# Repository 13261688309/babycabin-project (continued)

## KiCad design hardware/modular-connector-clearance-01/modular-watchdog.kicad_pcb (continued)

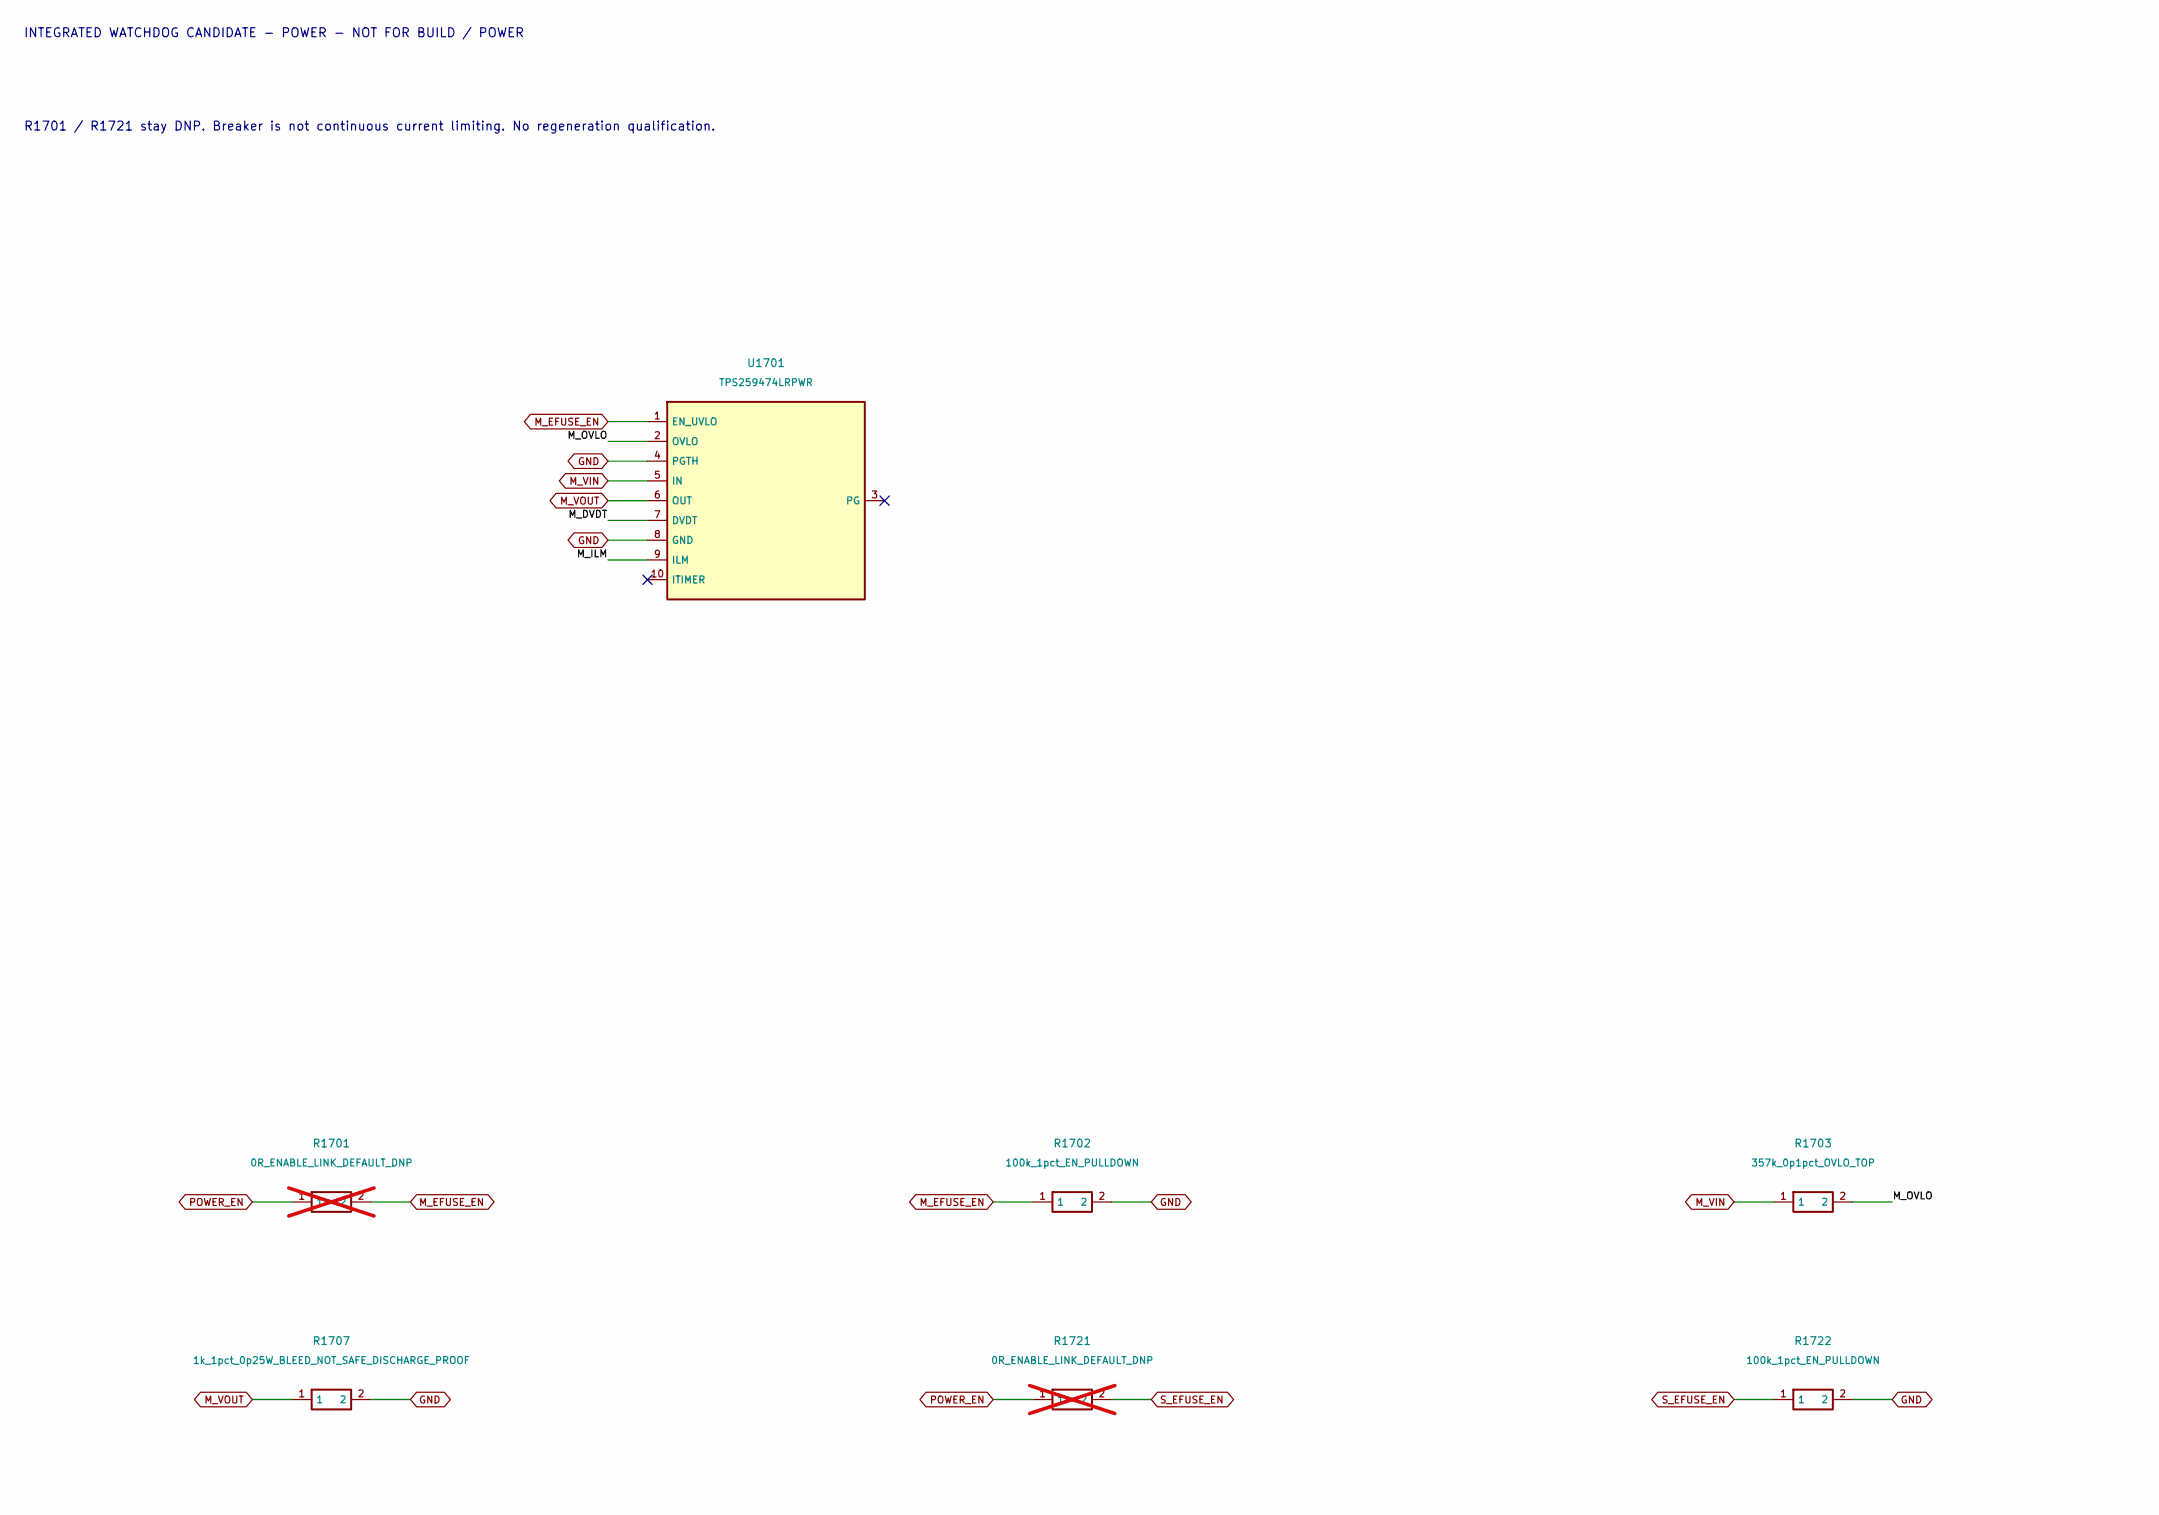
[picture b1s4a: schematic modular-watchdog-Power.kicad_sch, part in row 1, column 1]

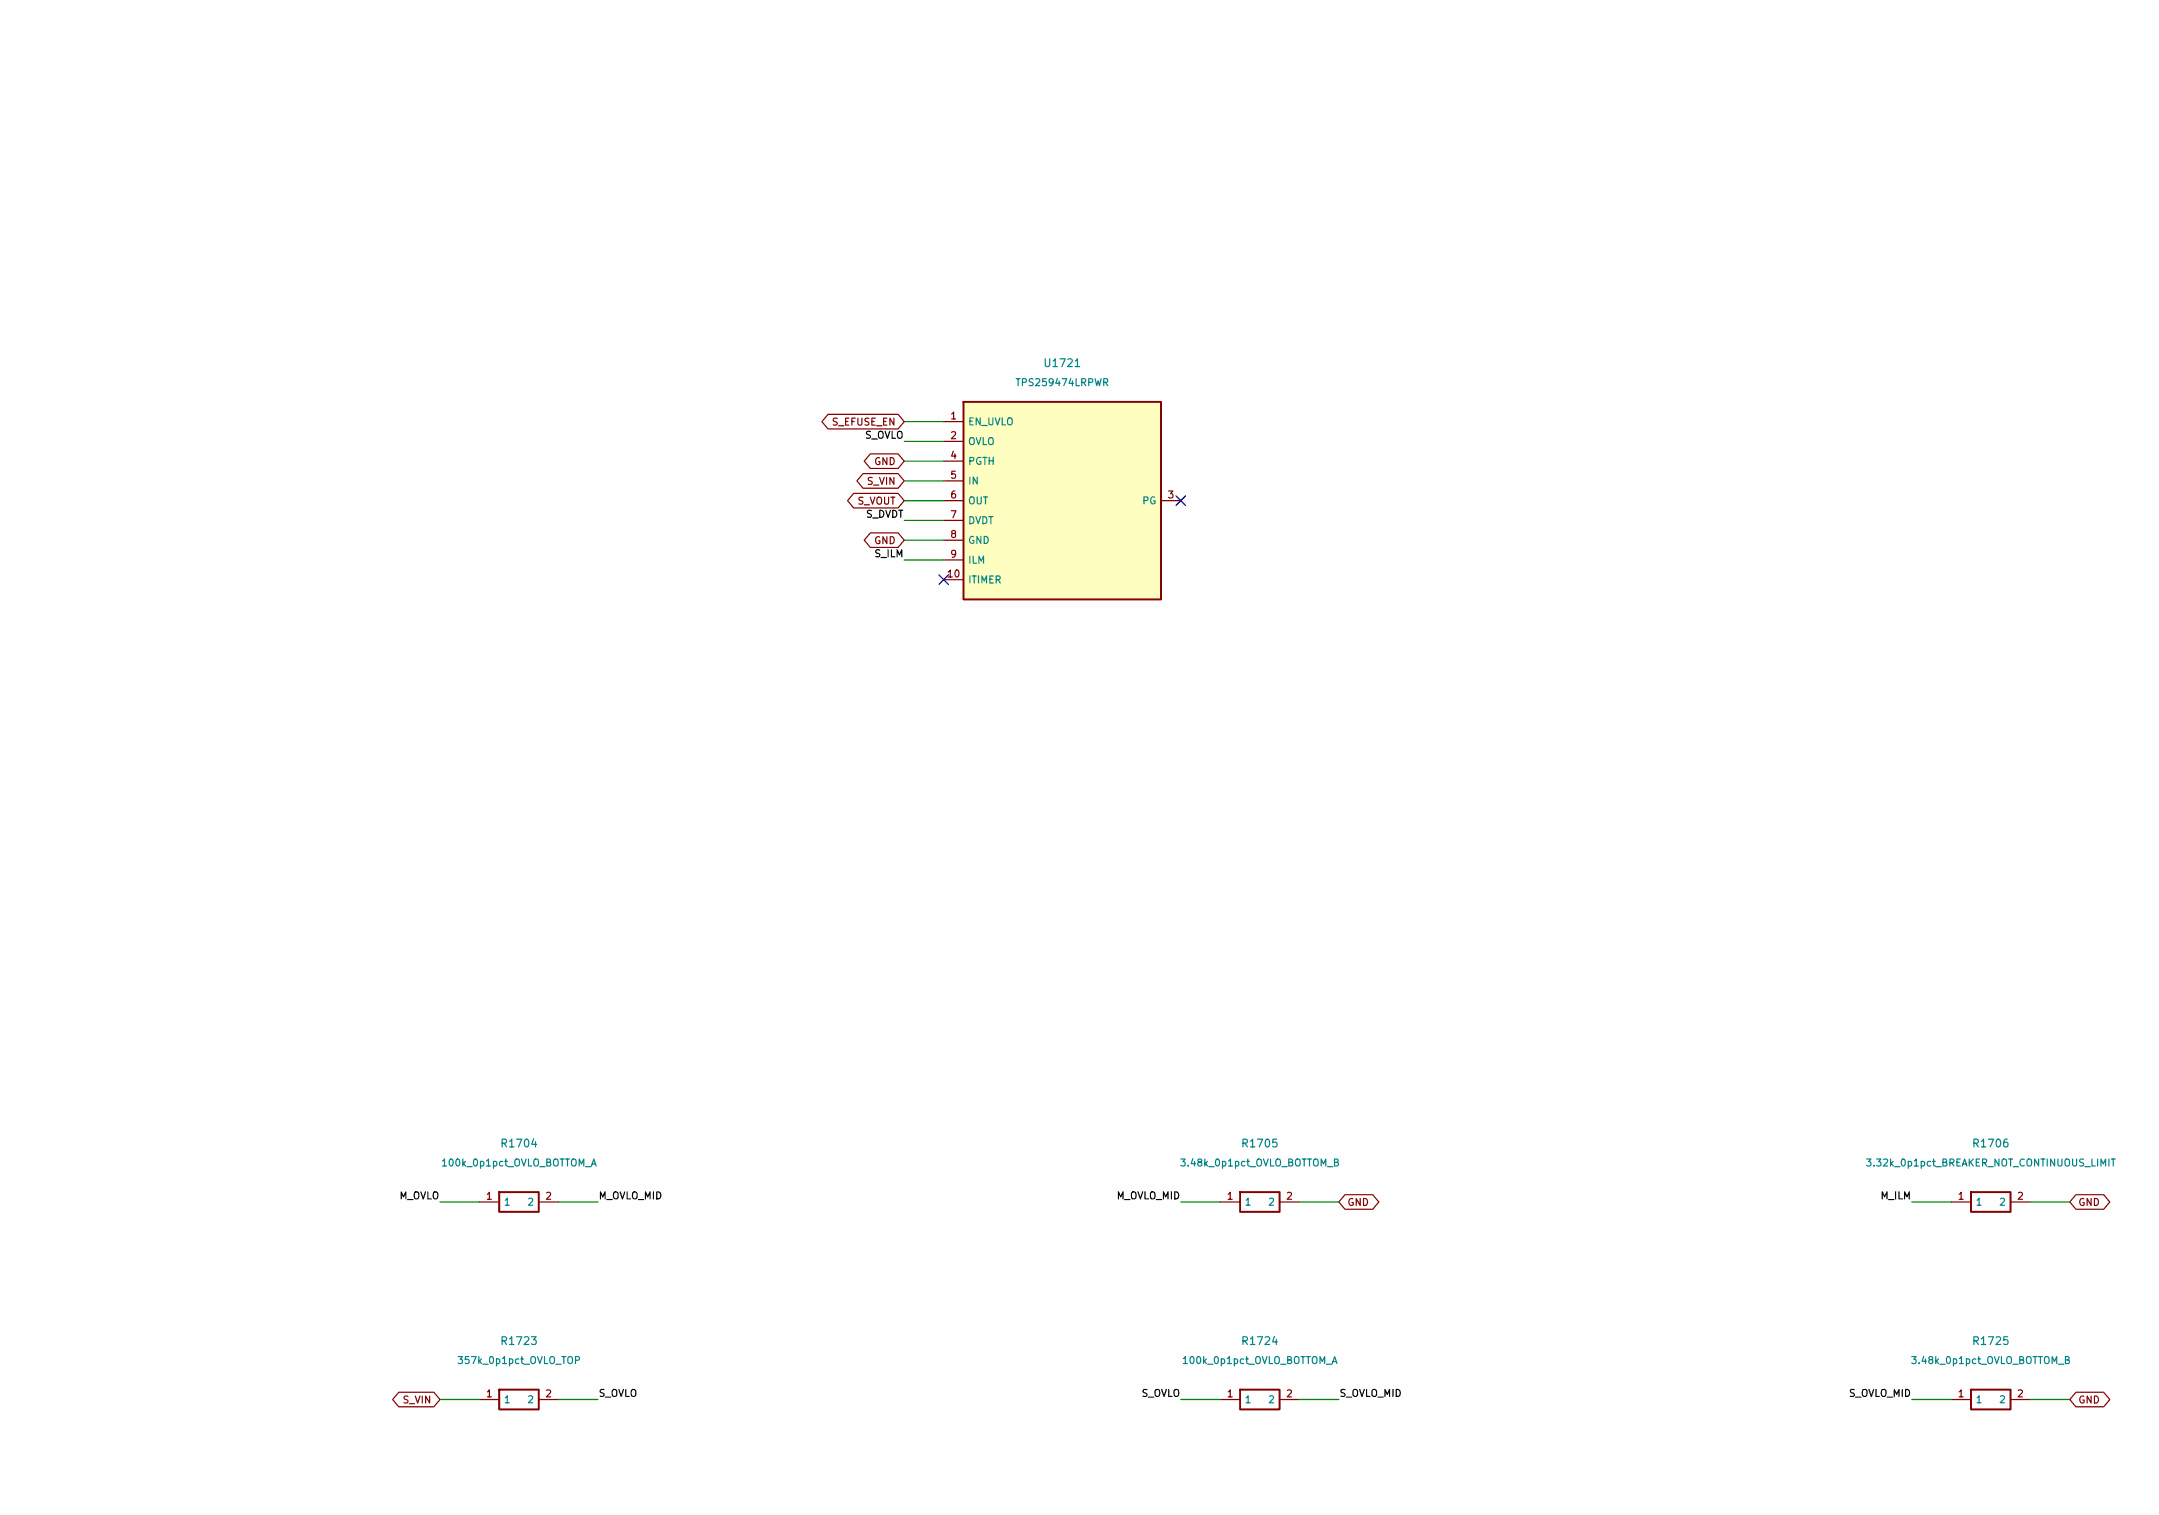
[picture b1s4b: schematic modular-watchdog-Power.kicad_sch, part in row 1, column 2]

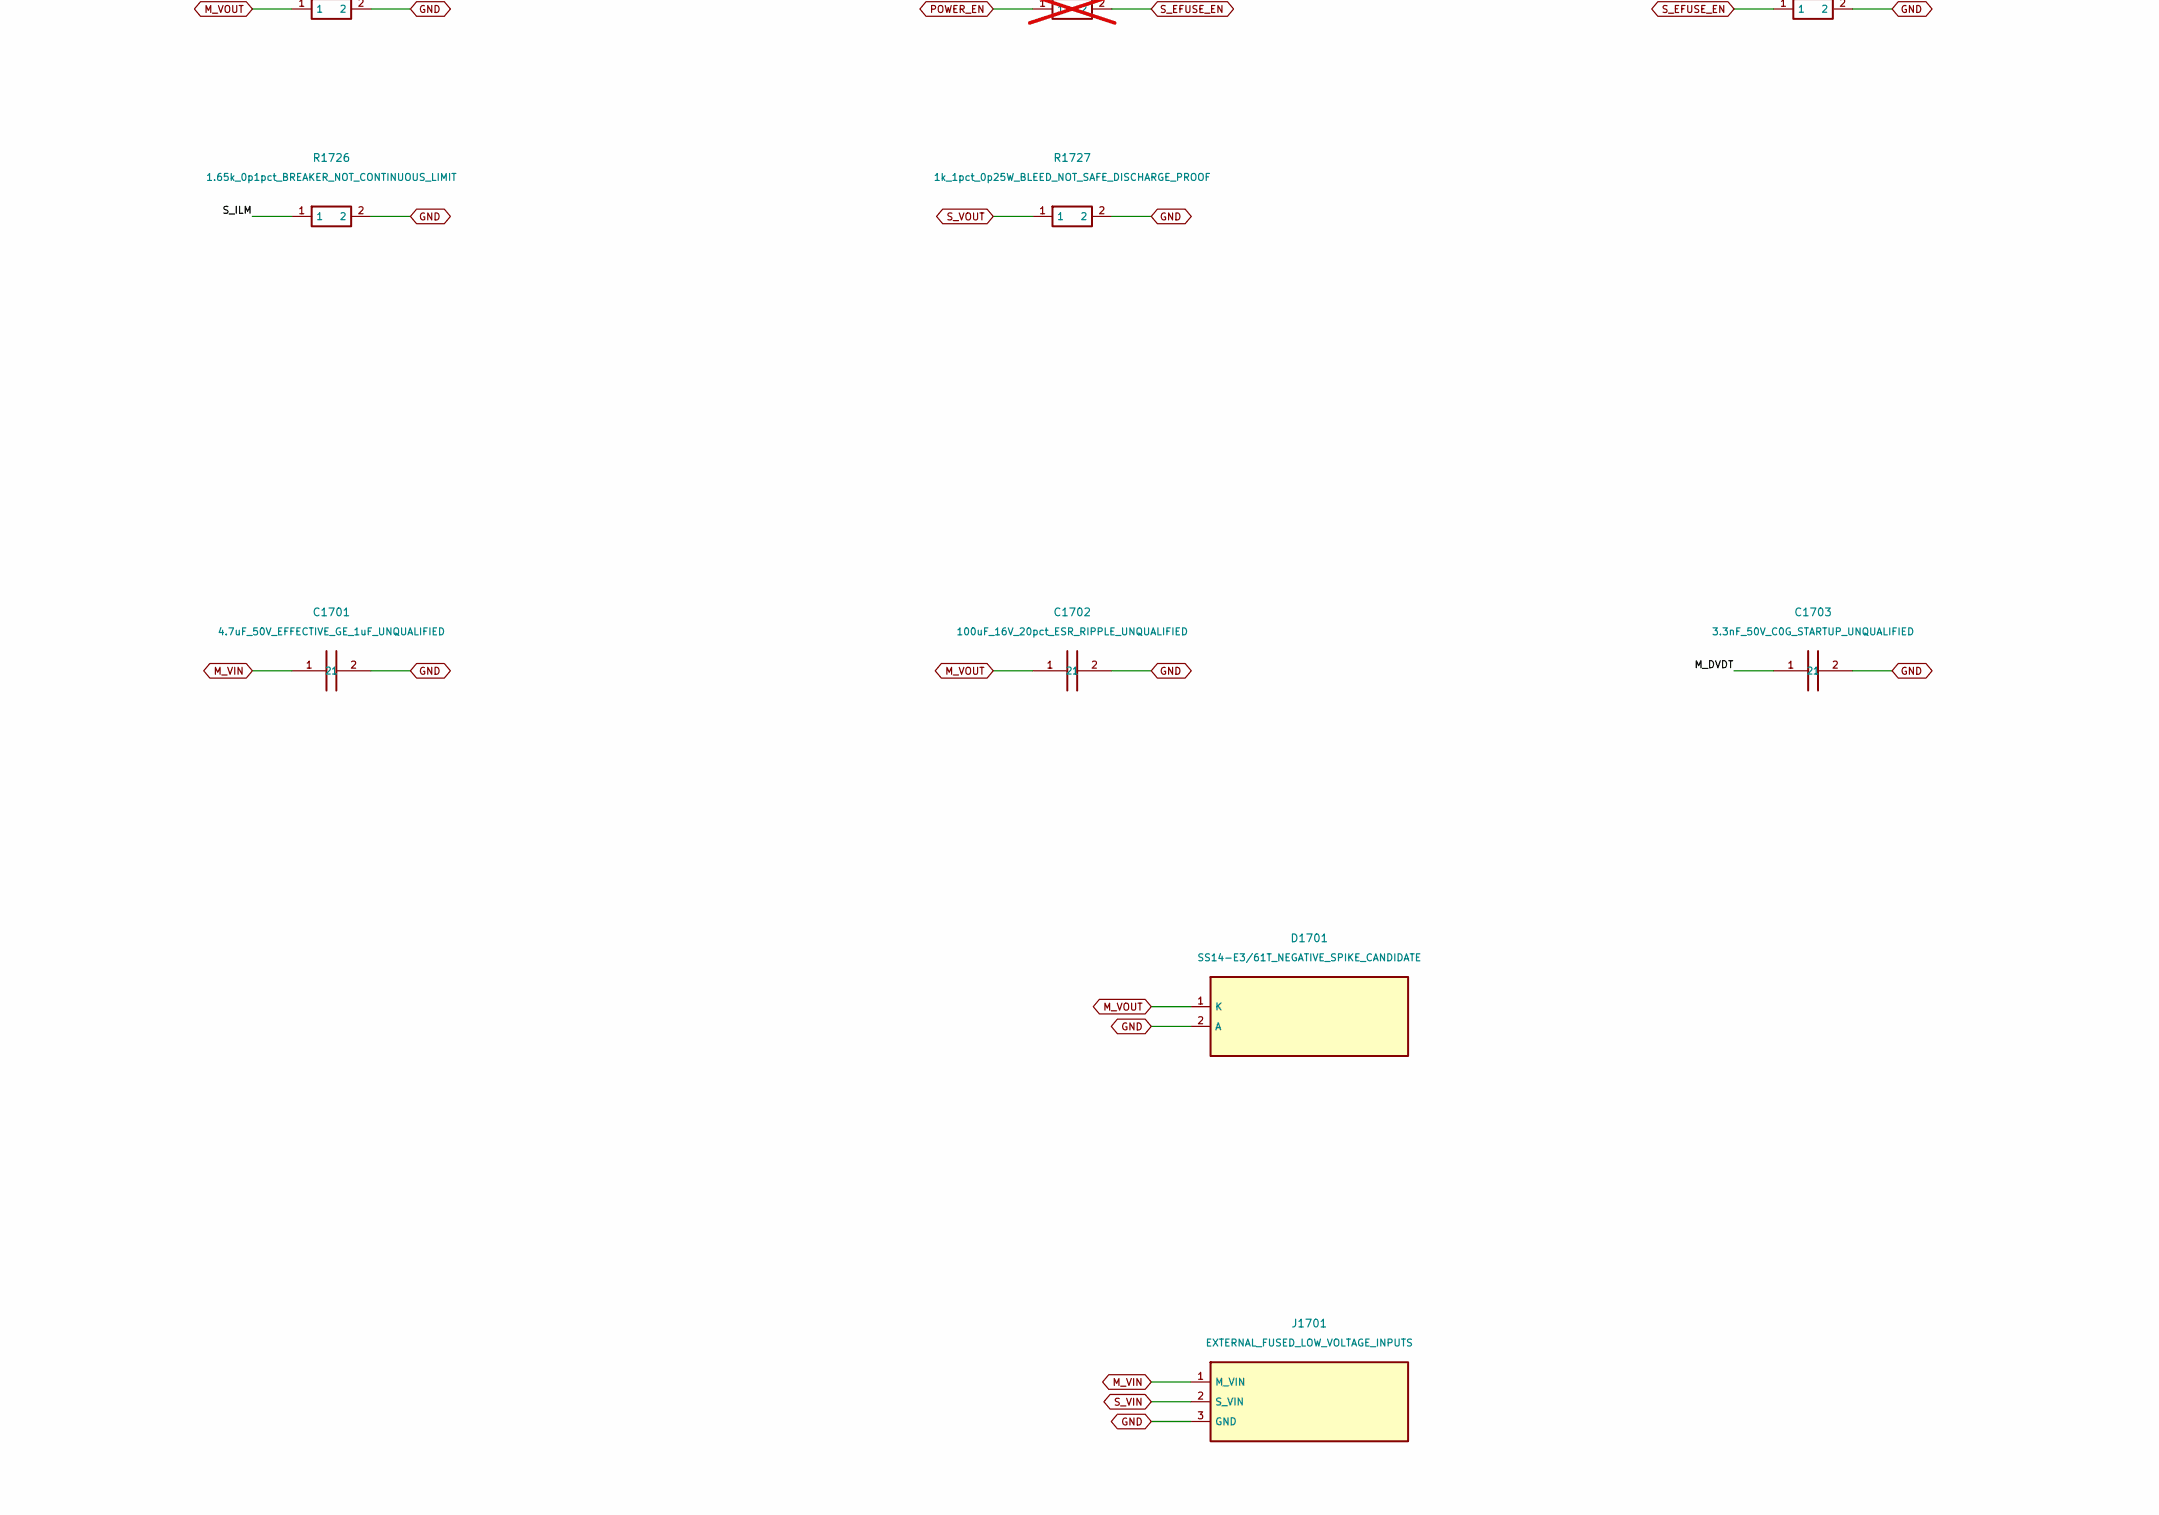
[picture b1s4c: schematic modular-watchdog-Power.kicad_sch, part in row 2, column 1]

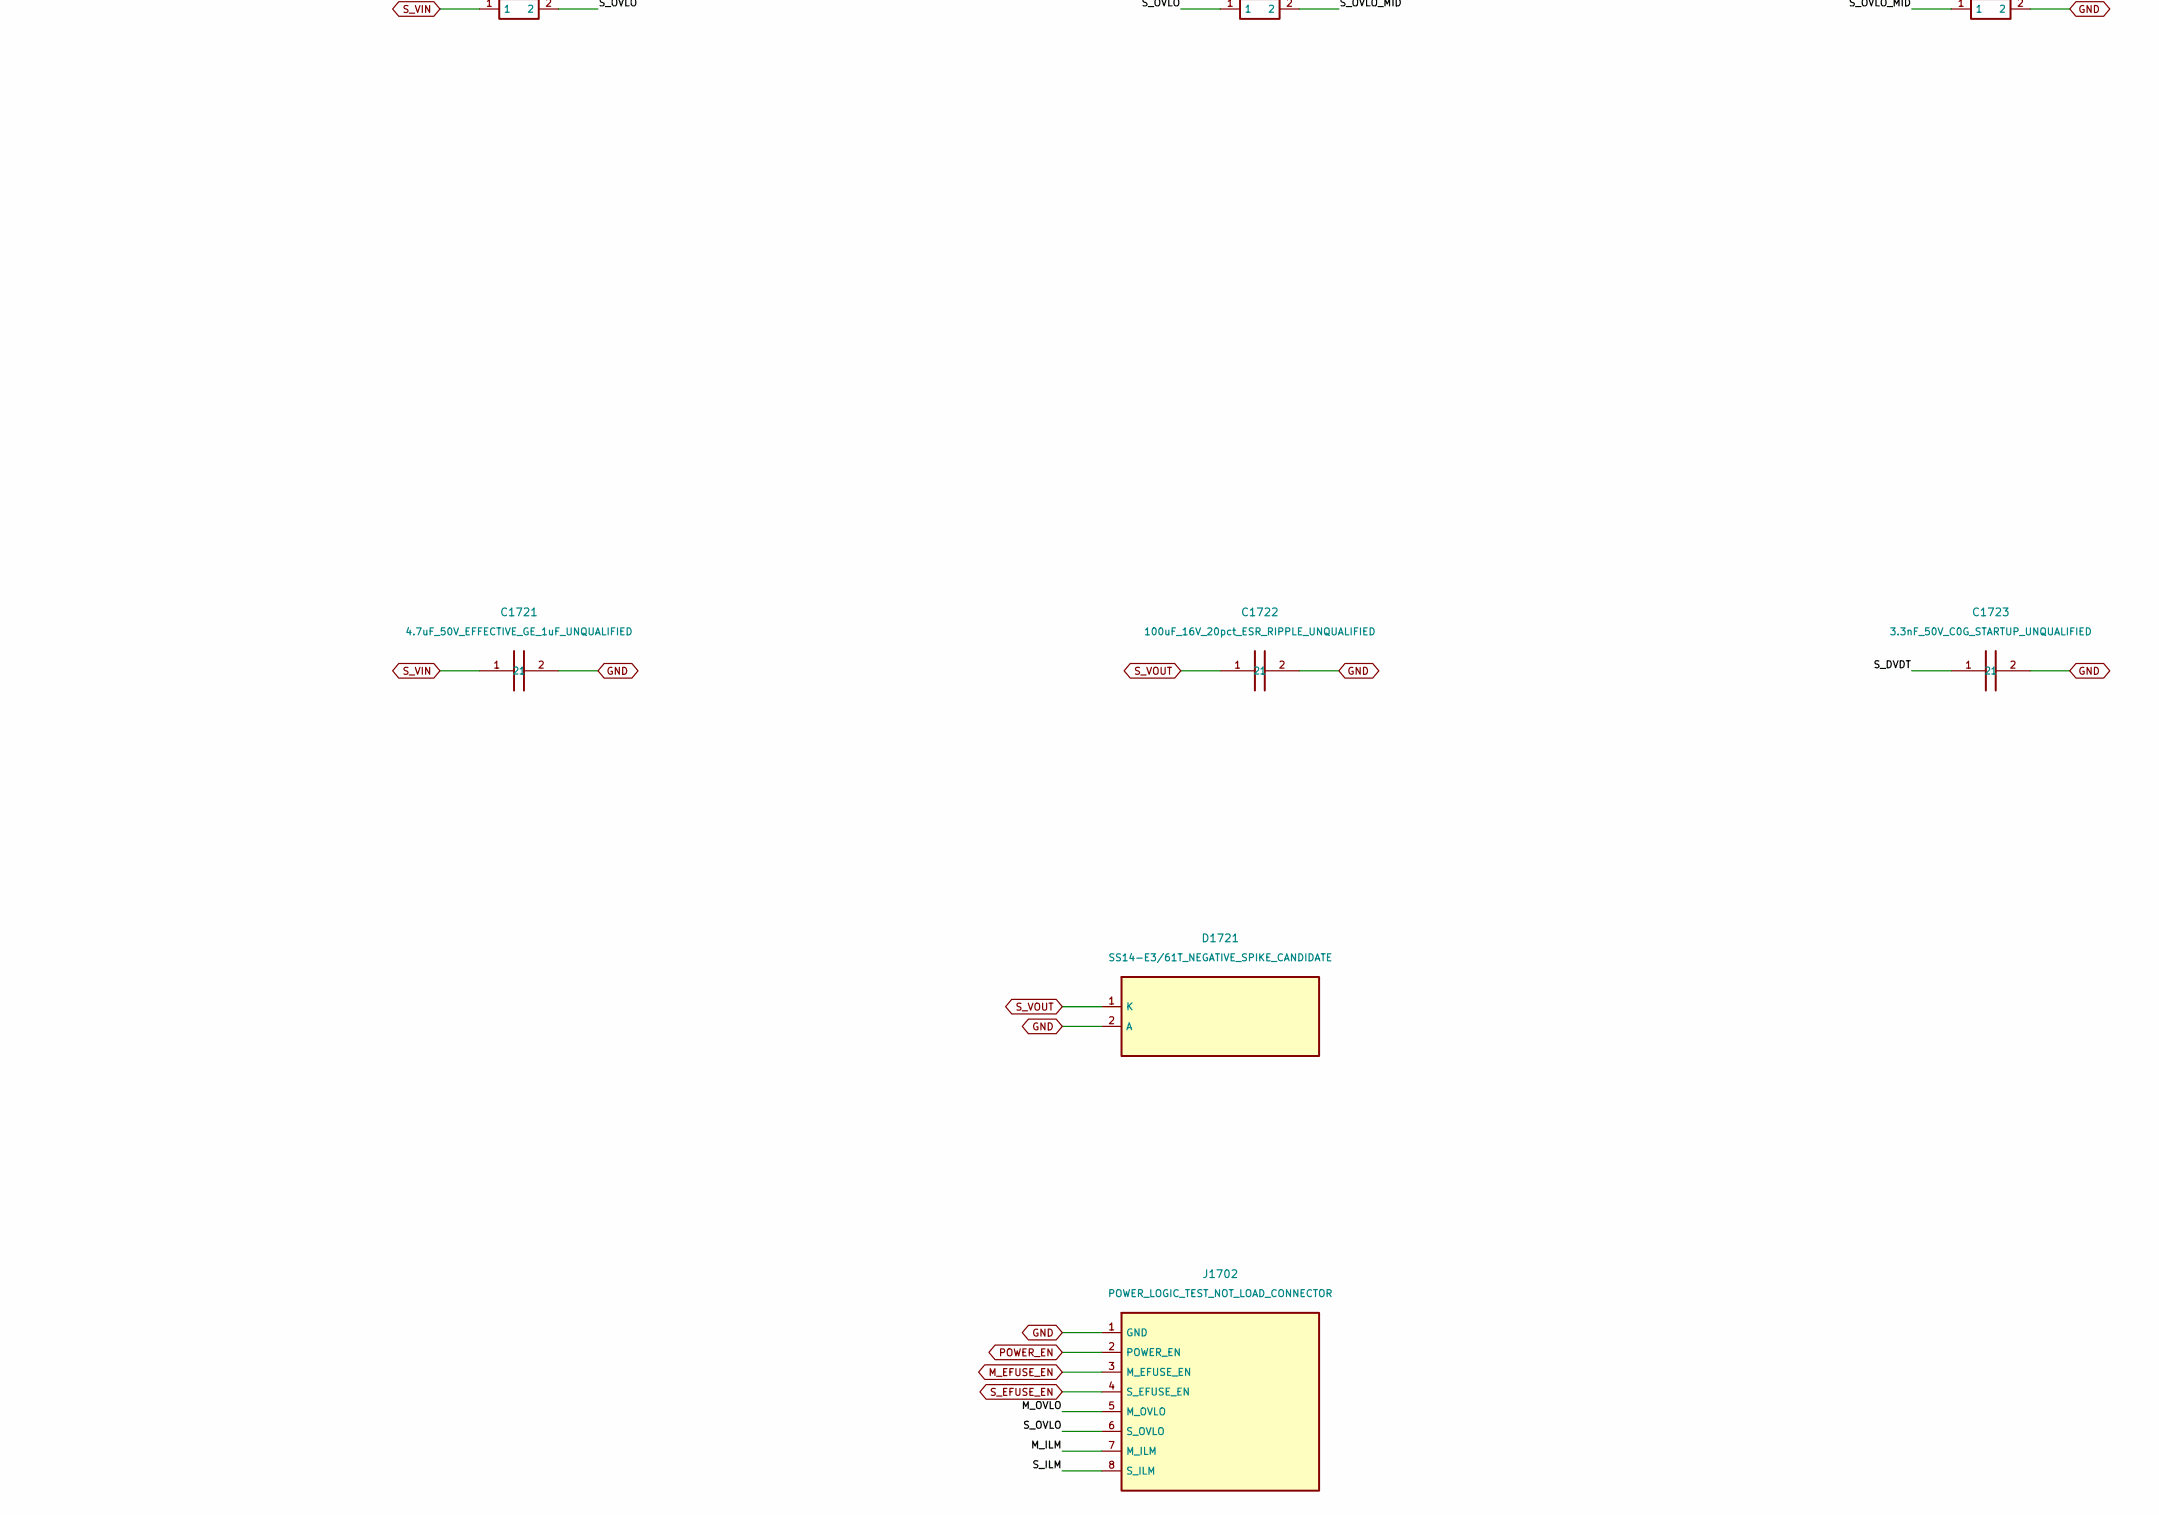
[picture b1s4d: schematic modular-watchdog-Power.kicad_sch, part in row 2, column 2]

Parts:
C1701, C1721: 4.7uF_50V_EFFECTIVE_GE_1uF_UNQUALIFIED; TDK_1206_Reflow_CapacitorDraft
C1702, C1722: 100uF_16V_20pct_ESR_RIPPLE_UNQUALIFIED; Panasonic_EEUFR1C101_D5_P2_StraightLead_CapacitorDraft
C1703, C1723: 3.3nF_50V_C0G_STARTUP_UNQUALIFIED; TDK_0805_Reflow_CapacitorDraft
D1701, D1721: SS14-E3/61T_NEGATIVE_SPIKE_CANDIDATE; Vishay_SS14_SMA_K1_DiscreteDraft
J1701: EXTERNAL_FUSED_LOW_VOLTAGE_INPUTS; TerminalBlock_Phoenix_MKDS-1,5-3-5.08_1x03_P5.08mm_Horizont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
J1702: POWER_LOGIC_TEST_NOT_LOAD_CONNECTOR; JST_PH_B8B-PH-K_1x08_P2.00mm_Vertical_ConnectorDraft
R1701, R1721: 0R_ENABLE_LINK_DEFAULT_DNP; Vishay_CRCW0805_Reflow_ResistorDraft; not fitted
R1702, R1722: 100k_1pct_EN_PULLDOWN; Vishay_CRCW0805_Reflow_ResistorDraft
R1703, R1723: 357k_0p1pct_OVLO_TOP; Vishay_TNPW0805_Reflow_ResistorDraft
R1704, R1724: 100k_0p1pct_OVLO_BOTTOM_A; Vishay_TNPW0805_Reflow_ResistorDraft
R1705, R1725: 3.48k_0p1pct_OVLO_BOTTOM_B; Vishay_TNPW0805_Reflow_ResistorDraft
R1706: 3.32k_0p1pct_BREAKER_NOT_CONTINUOUS_LIMIT; Vishay_TNPW0805_Reflow_ResistorDraft
R1707, R1727: 1k_1pct_0p25W_BLEED_NOT_SAFE_DISCHARGE_PROOF; Vishay_CRCW1206_Reflow_ResistorDraft
R1726: 1.65k_0p1pct_BREAKER_NOT_CONTINUOUS_LIMIT; Vishay_TNPW0805_Reflow_ResistorDraft
U1701, U1721: TPS259474LRPWR; TI_RPW0010A_SplitPaste_ModularPowerDraft

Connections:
/Power/M_DVDT: C1703.1, U1701.7 (DVDT)
/Power/M_ILM: J1702.7 (M_ILM), R1706.1, U1701.9 (ILM)
/Power/M_OVLO: J1702.5 (M_OVLO), R1703.2, R1704.1, U1701.2 (OVLO)
/Power/M_OVLO_MID: R1704.2, R1705.1
/Power/S_DVDT: C1723.1, U1721.7 (DVDT)
/Power/S_ILM: J1702.8 (S_ILM), R1726.1, U1721.9 (ILM)
/Power/S_OVLO: J1702.6 (S_OVLO), R1723.2, R1724.1, U1721.2 (OVLO)
/Power/S_OVLO_MID: R1724.2, R1725.1
GND: C1701.2, C1702.2, C1703.2, C1721.2, C1722.2, C1723.2, D1701.2 (A), D1721.2 (A), J1701.3 (GND), J1702.1 (GND), R1702.2, R1705.2, R1706.2, R1707.2, R1722.2, R1725.2, R1726.2, R1727.2, U1701.4 (PGTH), U1701.8 (GND), U1721.4 (PGTH), U1721.8 (GND); also elsewhere on the board
M_EFUSE_EN: J1702.3 (M_EFUSE_EN), R1701.2, R1702.1, U1701.1 (EN_UVLO); also elsewhere on the board
M_VIN: C1701.1, J1701.1 (M_VIN), R1703.1, U1701.5 (IN); also elsewhere on the board
M_VOUT: C1702.1, D1701.1 (K), R1707.1, U1701.6 (OUT); also elsewhere on the board
POWER_EN: J1702.2 (POWER_EN), R1701.1, R1721.1; also elsewhere on the board
S_EFUSE_EN: J1702.4 (S_EFUSE_EN), R1721.2, R1722.1, U1721.1 (EN_UVLO); also elsewhere on the board
S_VIN: C1721.1, J1701.2 (S_VIN), R1723.1, U1721.5 (IN); also elsewhere on the board
S_VOUT: C1722.1, D1721.1 (K), R1727.1, U1721.6 (OUT); also elsewhere on the board

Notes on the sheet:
INTEGRATED WATCHDOG CANDIDATE - POWER - NOT FOR BUILD / POWER
R1701 / R1721 stay DNP. Breaker is not continuous current limiting. No regeneration qualification.

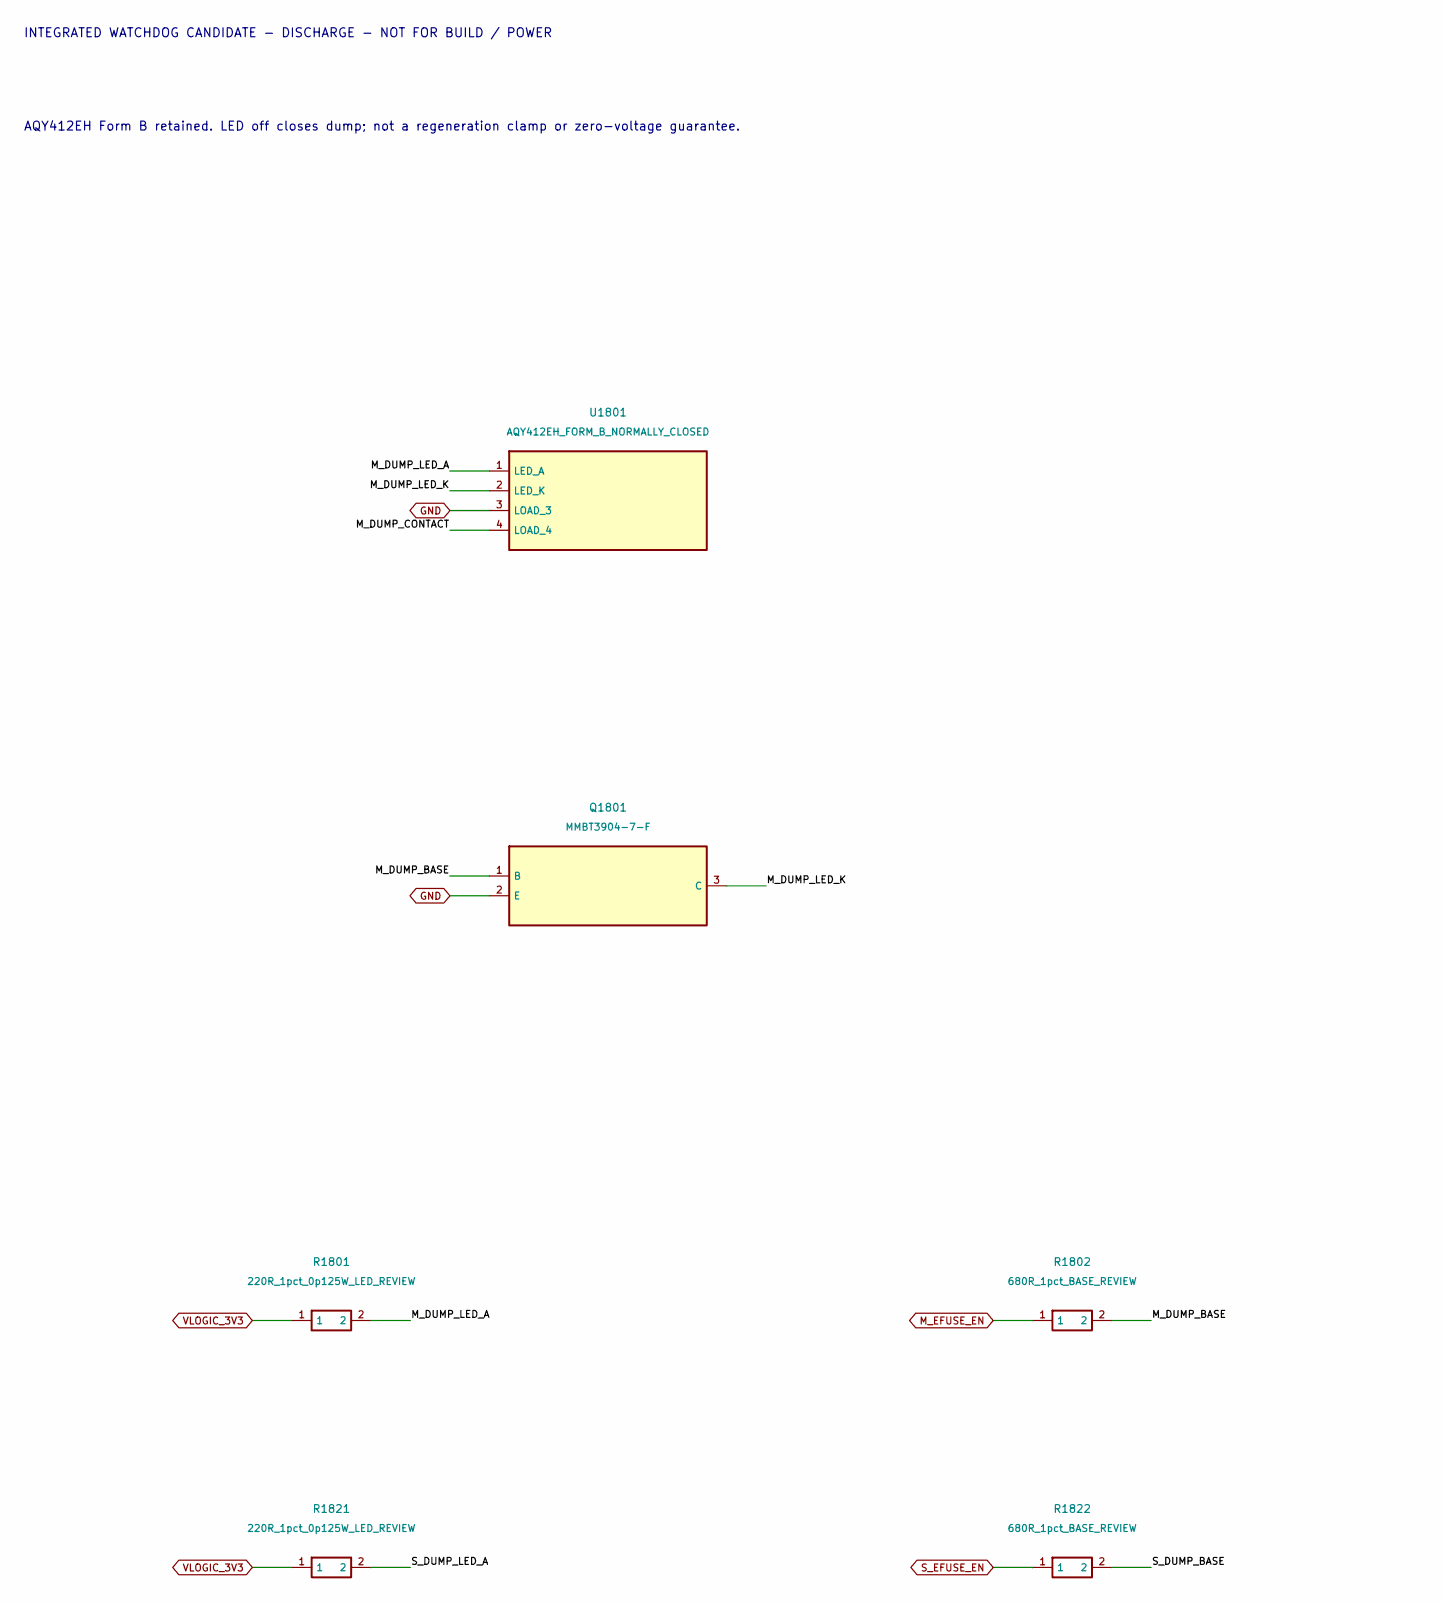
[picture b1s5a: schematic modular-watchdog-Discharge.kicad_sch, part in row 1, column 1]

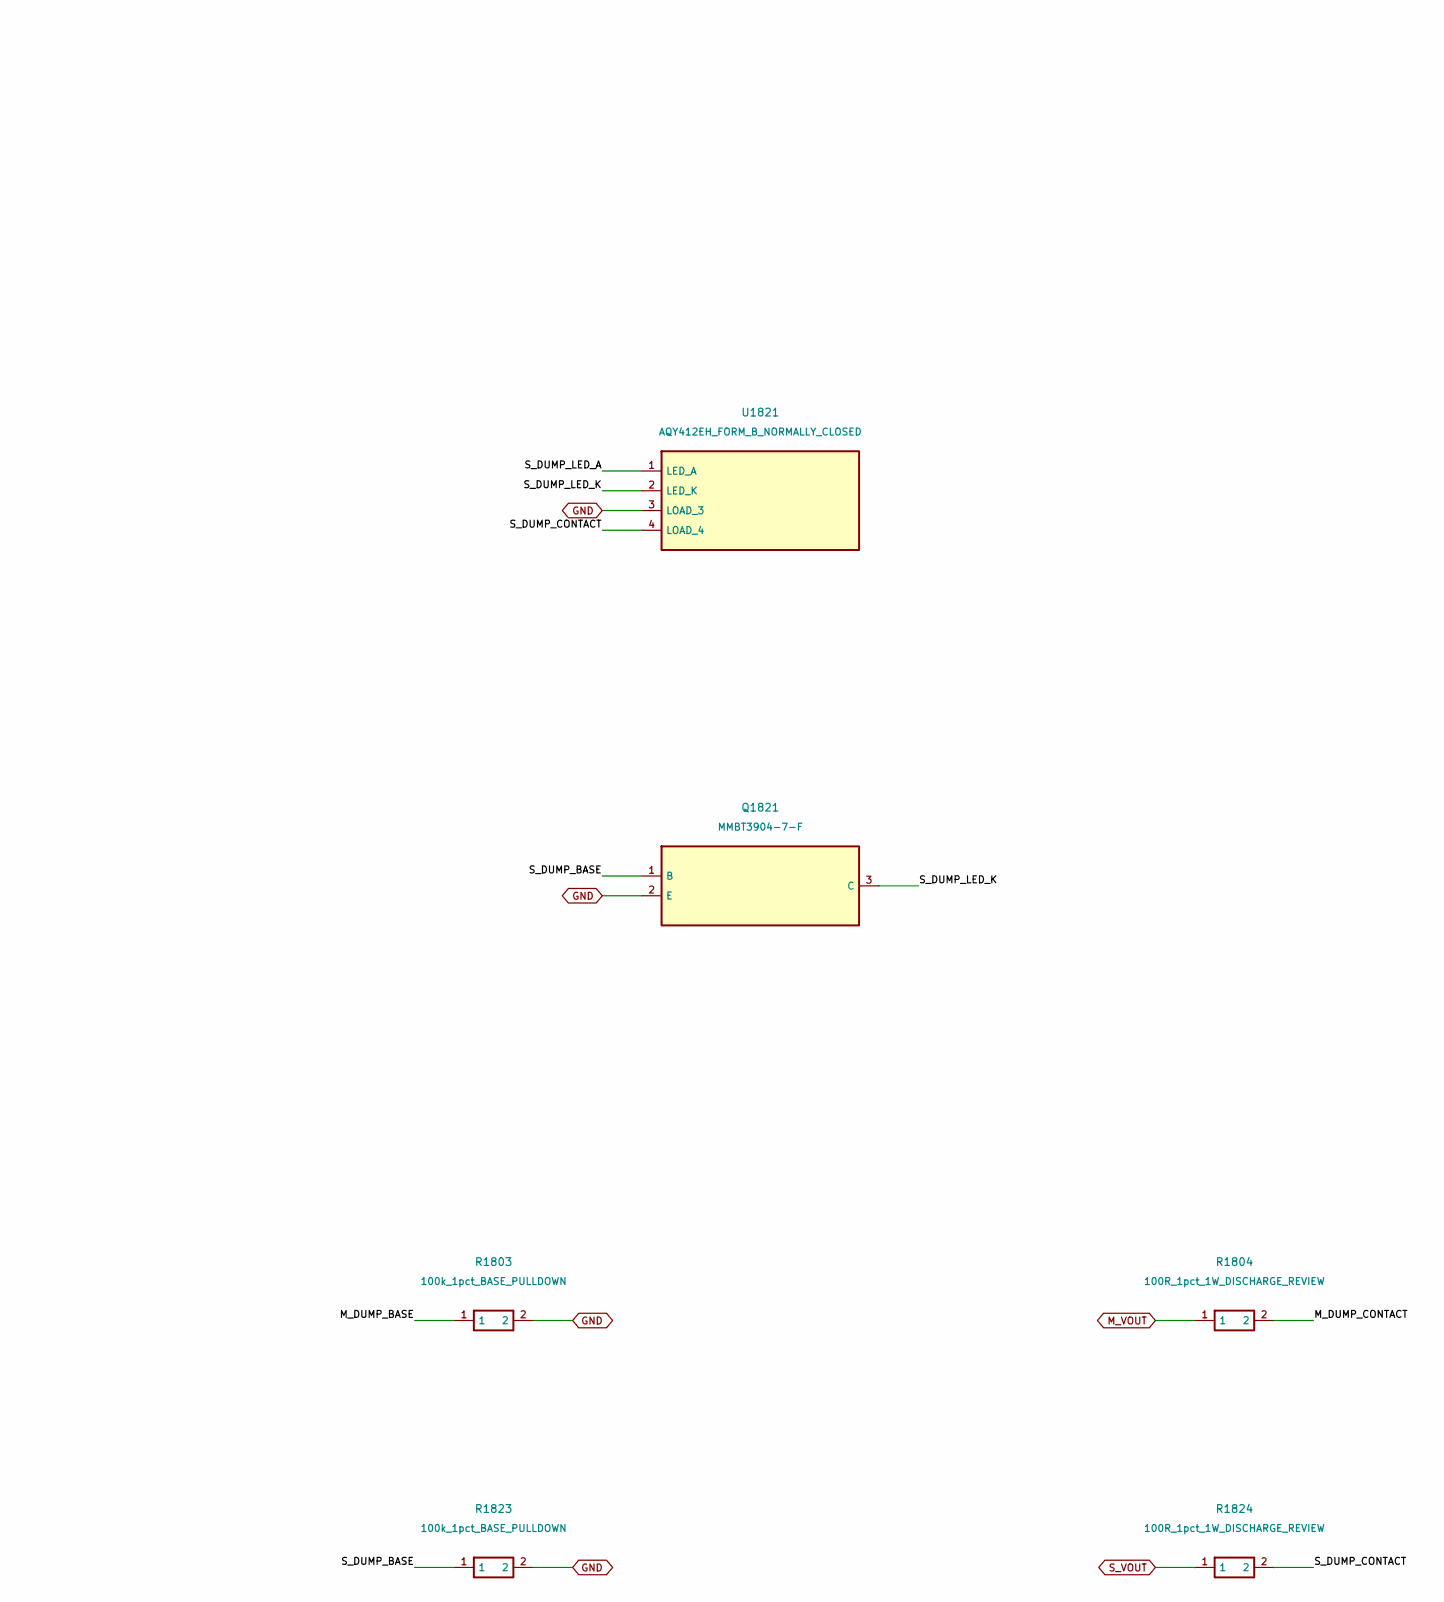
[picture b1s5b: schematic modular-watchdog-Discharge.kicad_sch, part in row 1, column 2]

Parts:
Q1801, Q1821: MMBT3904-7-F; Diodes_MMBT3904_SOT23_DiscreteDraft
R1801, R1821: 220R_1pct_0p125W_LED_REVIEW; Vishay_CRCW0805_Reflow_ResistorDraft
R1802, R1822: 680R_1pct_BASE_REVIEW; Vishay_CRCW0805_Reflow_ResistorDraft
R1803, R1823: 100k_1pct_BASE_PULLDOWN; Vishay_CRCW0805_Reflow_ResistorDraft
R1804, R1824: 100R_1pct_1W_DISCHARGE_REVIEW; Vishay_CRCW2512_Reflow_ResistorDraft
U1801, U1821: AQY412EH_FORM_B_NORMALLY_CLOSED; Panasonic_AQY412EH_DIP4_ModularPowerDraft

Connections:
/Discharge/M_DUMP_BASE: Q1801.1 (B), R1802.2, R1803.1
/Discharge/M_DUMP_CONTACT: R1804.2, U1801.4 (LOAD_4)
/Discharge/M_DUMP_LED_A: R1801.2, U1801.1 (LED_A)
/Discharge/M_DUMP_LED_K: Q1801.3 (C), U1801.2 (LED_K)
/Discharge/S_DUMP_BASE: Q1821.1 (B), R1822.2, R1823.1
/Discharge/S_DUMP_CONTACT: R1824.2, U1821.4 (LOAD_4)
/Discharge/S_DUMP_LED_A: R1821.2, U1821.1 (LED_A)
/Discharge/S_DUMP_LED_K: Q1821.3 (C), U1821.2 (LED_K)
GND: Q1801.2 (E), Q1821.2 (E), R1803.2, R1823.2, U1801.3 (LOAD_3), U1821.3 (LOAD_3); also elsewhere on the board
M_EFUSE_EN: R1802.1; also elsewhere on the board
M_VOUT: R1804.1; also elsewhere on the board
S_EFUSE_EN: R1822.1; also elsewhere on the board
S_VOUT: R1824.1; also elsewhere on the board
VLOGIC_3V3: R1801.1, R1821.1; also elsewhere on the board

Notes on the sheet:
INTEGRATED WATCHDOG CANDIDATE - DISCHARGE - NOT FOR BUILD / POWER
AQY412EH Form B retained. LED off closes dump; not a regeneration clamp or zero-voltage guarantee.
